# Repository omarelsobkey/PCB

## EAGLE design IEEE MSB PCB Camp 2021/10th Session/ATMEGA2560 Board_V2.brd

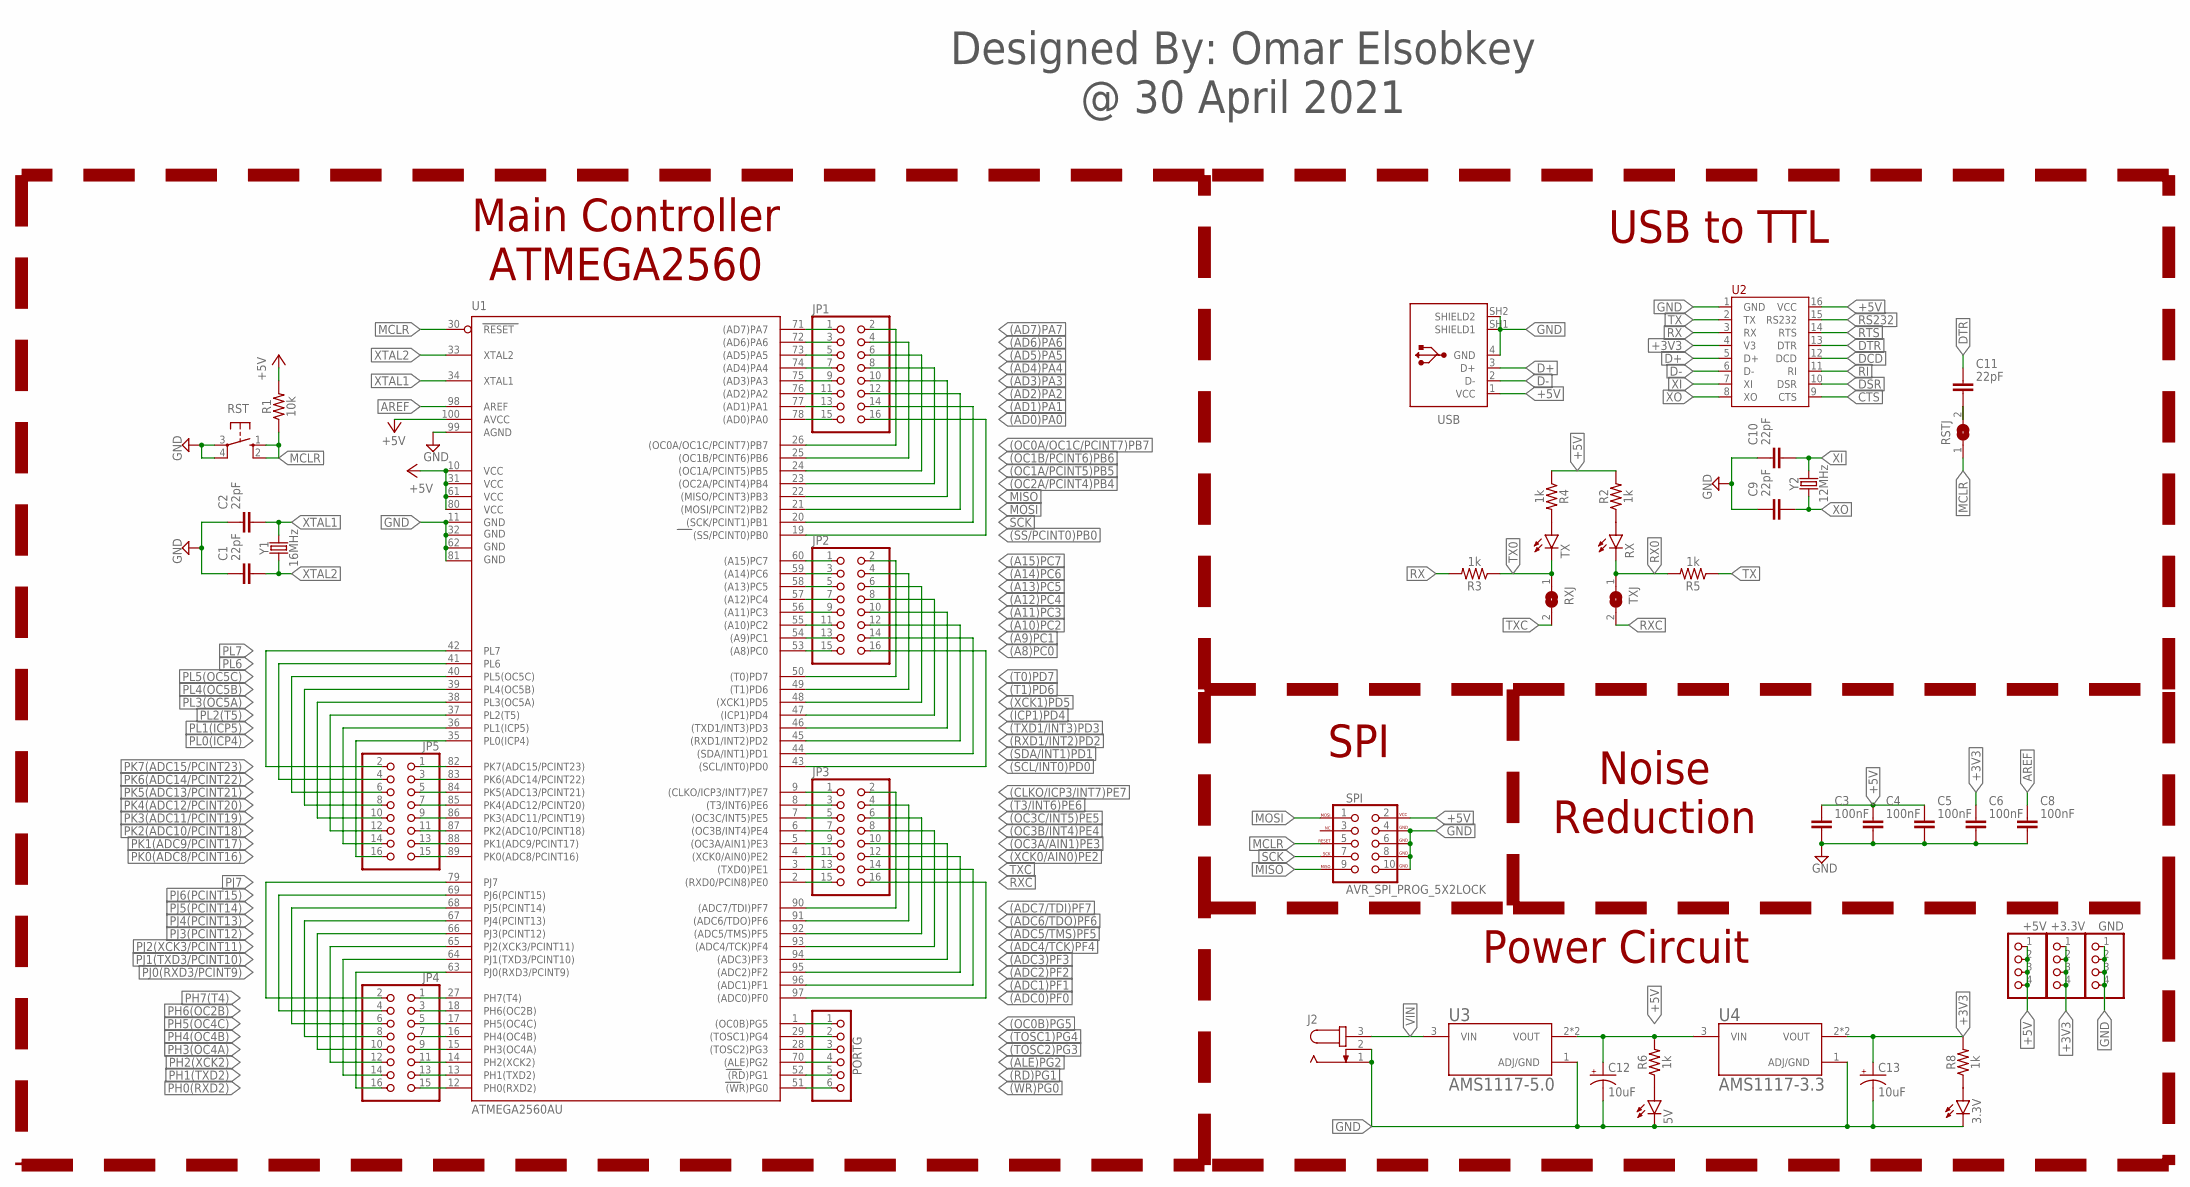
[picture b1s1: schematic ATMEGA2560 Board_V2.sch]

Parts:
3.3V, 5V: LEDCHIP-LED0805; CHIP-LED0805
+3.3V, +5V: PINHD-1X4; 1X04
C1, C2, C9, C10, C11: 22pF; CAPC2012X110
C3, C4, C5, C6, C8: 100nF; CAPC2012X110
C12, C13: 10uF; CPOL-RADIAL-2.5MM-5MM-KIT
GND: PINHD-1X4; 1X04
J2: JACK-PLUG0; SPC4077
JP1, JP2, JP3, JP4, JP5: PINHD-2X8; 2X08
PORTG: PINHD-1X6; 1X06
R1: 10k; 1206
R2, R3, R4, R5, R6, R8: 1k; 1206
RST: 10-XX; B3F-10XX
RSTJ: SJW
RX: LEDCHIP-LED0805; CHIP-LED0805
RXJ: SJW
SPI: AVR_SPI_PROG_5X2LOCK; 2X5-SHROUDED_LOCK
TX: LEDCHIP-LED0805; CHIP-LED0805
TXJ: SJW
U1: ATMEGA2560AU; TQFP100
U2: CH340G; SOP-16
U3: AMS1117-5.0
U4: AMS1117-3.3; AMS1117-5.0
USB: 61729-1011; 61729-1011BLF
Y1: 16MHz; HC49U
Y2: 12MHz; HC49U

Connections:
(A8)PC0: JP2.15, U1.53 ((A8)PC0)
(A9)PC1: JP2.13, U1.54 ((A9)PC1)
(A10)PC2: JP2.11, U1.55 ((A10)PC2)
(A11)PC3: JP2.9, U1.56 ((A11)PC3)
(A12)PC4: JP2.7, U1.57 ((A12)PC4)
(A13)PC5: JP2.5, U1.58 ((A13)PC5)
(A14)PC6: JP2.3, U1.59 ((A14)PC6)
(A15)PC7: JP2.1, U1.60 ((A15)PC7)
(AD0)PA0: JP1.15, U1.78 ((AD0)PA0)
(AD1)PA1: JP1.13, U1.77 ((AD1)PA1)
(AD2)PA2: JP1.11, U1.76 ((AD2)PA2)
(AD3)PA3: JP1.9, U1.75 ((AD3)PA3)
(AD4)PA4: JP1.7, U1.74 ((AD4)PA4)
(AD5)PA5: JP1.5, U1.73 ((AD5)PA5)
(AD6)PA6: JP1.3, U1.72 ((AD6)PA6)
(AD7)PA7: JP1.1, U1.71 ((AD7)PA7)
(ADC0)PF0: JP3.16, U1.97 ((ADC0)PF0)
(ADC1)PF1: JP3.14, U1.96 ((ADC1)PF1)
(ADC2)PF2: JP3.12, U1.95 ((ADC2)PF2)
(ADC3)PF3: JP3.10, U1.94 ((ADC3)PF3)
(ADC4/TCK)PF4: JP3.8, U1.93 ((ADC4/TCK)PF4)
(ADC5/TMS)PF5: JP3.6, U1.92 ((ADC5/TMS)PF5)
(ADC6/TDO)PF6: JP3.4, U1.91 ((ADC6/TDO)PF6)
(ADC7/TDI)PF7: JP3.2, U1.90 ((ADC7/TDI)PF7)
(ALE)PG2: PORTG.4, U1.70 ((ALE)PG2)
(CLKO/ICP3/INT7)PE7: JP3.1, U1.9 ((CLKO/ICP3/INT7)PE7)
(ICP1)PD4: JP2.8, U1.47 ((ICP1)PD4)
(OC0A/OC1C/PCINT7)PB7: JP1.2, U1.26 ((OC0A/OC1C/PCINT7)PB7)
(OC0B)PG5: PORTG.1, U1.1 ((OC0B)PG5)
(OC1A/PCINT5)PB5: JP1.6, U1.24 ((OC1A/PCINT5)PB5)
(OC1B/PCINT6)PB6: JP1.4, U1.25 ((OC1B/PCINT6)PB6)
(OC2A/PCINT4)PB4: JP1.8, U1.23 ((OC2A/PCINT4)PB4)
(OC3A/AIN1)PE3: JP3.9, U1.5 ((OC3A/AIN1)PE3)
(OC3B/INT4)PE4: JP3.7, U1.6 ((OC3B/INT4)PE4)
(OC3C/INT5)PE5: JP3.5, U1.7 ((OC3C/INT5)PE5)
(RD)PG1: PORTG.5, U1.52 ((RD)PG1)
(RXD1/INT2)PD2: JP2.12, U1.45 ((RXD1/INT2)PD2)
(SCL/INT0)PD0: JP2.16, U1.43 ((SCL/INT0)PD0)
(SDA/INT1)PD1: JP2.14, U1.44 ((SDA/INT1)PD1)
(SS/PCINT0)PB0: JP1.16, U1.19 ((SS/PCINT0)PB0)
(T0)PD7: JP2.2, U1.50 ((T0)PD7)
(T1)PD6: JP2.4, U1.49 ((T1)PD6)
(T3/INT6)PE6: JP3.3, U1.8 ((T3/INT6)PE6)
(TOSC1)PG4: PORTG.2, U1.29 ((TOSC1)PG4)
(TOSC2)PG3: PORTG.3, U1.28 ((TOSC2)PG3)
(TXD1/INT3)PD3: JP2.10, U1.46 ((TXD1/INT3)PD3)
(WR)PG0: PORTG.6, U1.51 ((WR)PG0)
(XCK0/AIN0)PE2: JP3.11, U1.4 ((XCK0/AIN0)PE2)
(XCK1)PD5: JP2.6, U1.48 ((XCK1)PD5)
+3V3: +3.3V.1, +3.3V.2, +3.3V.3, +3.3V.4, C6.1, C13.1 (+), R8.2, U2.4 (V3), U4.2 (VOUT), U4.4 (VOUT)
+5V: +5V.1, +5V.2, +5V.3, +5V.4, C3.1, C4.1, C5.1, C12.1 (+), R1.2, R2.2, R4.1, R6.2, SPI.2 (VCC), U1.10 (VCC), U1.31 (VCC1), U1.61 (VCC2), U1.80 (VCC3), U1.100 (AVCC), U2.16 (VCC), U3.2 (VOUT), U3.4 (VOUT), U4.3 (VIN), USB.1 (VCC)
AREF: C8.1, U1.98 (AREF)
CTS: U2.9 (CTS)
D+: U2.5 (D+), USB.3 (D+)
D-: U2.6 (D-), USB.2 (D-)
DCD: U2.12 (DCD)
DSR: U2.10 (DSR)
DTR: C11.1, U2.13 (DTR)
GND: 3.3V.C, 5V.C, C1.1, C2.1, C3.2, C4.2, C5.2, C6.2, C8.2, C9.1, C10.1, C12.2 (-), C13.2 (-), GND.1, GND.2, GND.3, GND.4, J2.1, J2.2, RST.3, RST.4 (P1), SPI.4 (GND), SPI.6 (GND), SPI.8 (GND), SPI.10 (GND), U1.11 (GND), U1.32 (GND1), U1.62 (GND2), U1.81 (GND3), U1.99 (AGND), U2.1 (GND), U3.1 (ADJ/GND), U4.1 (ADJ/GND), USB.4 (GND), USB.SH1 (SHIELD1), USB.SH2 (SHIELD2)
MCLR: R1.1, RST.1 (S), RST.2 (S1), RSTJ.1, SPI.5 (RESET), U1.30 (RESET)
MISO: JP1.10, SPI.9 (MISO), U1.22 ((MISO/PCINT3)PB3)
MOSI: JP1.12, SPI.1 (MOSI), U1.21 ((MOSI/PCINT2)PB2)
unnamed: R2.1, RX.A
unnamed: R4.2, TX.A
unnamed: 5V.A, R6.1
unnamed: 3.3V.A, R8.1
unnamed: C11.2, RSTJ.2
PH0(RXD2): JP4.15, U1.12 (PH0(RXD2))
PH1(TXD2): JP4.13, U1.13 (PH1(TXD2))
PH2(XCK2): JP4.11, U1.14 (PH2(XCK2))
PH3(OC4A): JP4.9, U1.15 (PH3(OC4A))
PH4(OC4B): JP4.7, U1.16 (PH4(OC4B))
PH5(OC4C): JP4.5, U1.17 (PH5(OC4C))
PH6(OC2B): JP4.3, U1.18 (PH6(OC2B))
PH7(T4): JP4.1, U1.27 (PH7(T4))
PJ0(RXD3/PCINT9): JP4.16, U1.63 (PJ0(RXD3/PCINT9))
PJ1(TXD3/PCINT10): JP4.14, U1.64 (PJ1(TXD3/PCINT10))
PJ2(XCK3/PCINT11): JP4.12, U1.65 (PJ2(XCK3/PCINT11))
PJ3(PCINT12): JP4.10, U1.66 (PJ3(PCINT12))
PJ4(PCINT13): JP4.8, U1.67 (PJ4(PCINT13))
PJ5(PCINT14): JP4.6, U1.68 (PJ5(PCINT14))
PJ6(PCINT15): JP4.4, U1.69 (PJ6(PCINT15))
PJ7: JP4.2, U1.79 (PJ7)
PK0(ADC8/PCINT16): JP5.15, U1.89 (PK0(ADC8/PCINT16))
PK1(ADC9/PCINT17): JP5.13, U1.88 (PK1(ADC9/PCINT17))
PK2(ADC10/PCINT18): JP5.11, U1.87 (PK2(ADC10/PCINT18))
PK3(ADC11/PCINT19): JP5.9, U1.86 (PK3(ADC11/PCINT19))
PK4(ADC12/PCINT20): JP5.7, U1.85 (PK4(ADC12/PCINT20))
PK5(ADC13/PCINT21): JP5.5, U1.84 (PK5(ADC13/PCINT21))
PK6(ADC14/PCINT22): JP5.3, U1.83 (PK6(ADC14/PCINT22))
PK7(ADC15/PCINT23): JP5.1, U1.82 (PK7(ADC15/PCINT23))
PL0(ICP4): JP5.16, U1.35 (PL0(ICP4))
PL1(ICP5): JP5.14, U1.36 (PL1(ICP5))
PL2(T5): JP5.12, U1.37 (PL2(T5))
PL3(OC5A): JP5.10, U1.38 (PL3(OC5A))
PL4(OC5B): JP5.8, U1.39 (PL4(OC5B))
PL5(OC5C): JP5.6, U1.40 (PL5(OC5C))
PL6: JP5.4, U1.41 (PL6)
PL7: JP5.2, U1.42 (PL7)
RI: U2.11 (RI)
RS232: U2.15 (RS232)
RTS: U2.14 (RTS)
RX: R3.2, U2.3 (RX)
RX0: R5.2, RX.C, TXJ.1
RXC: JP3.15, TXJ.2, U1.2 ((RXD0/PCIN8)PE0)
SCK: JP1.14, SPI.7 (SCK), U1.20 ((SCK/PCINT1)PB1)
TX: R5.1, U2.2 (TX)
TX0: R3.1, RXJ.1, TX.C
TXC: JP3.13, RXJ.2, U1.3 ((TXD0)PE1)
VIN: J2.3, U3.3 (VIN)
XI: C10.2, U2.7 (XI), Y2.2
XO: C9.2, U2.8 (XO), Y2.1
XTAL1: C2.2, U1.34 (XTAL1), Y1.2
XTAL2: C1.2, U1.33 (XTAL2), Y1.1

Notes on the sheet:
Main Controller ATMEGA2560
USB to TTL
SPI
Noise Reduction
Power Circuit
Designed By: Omar Elsobkey @ 30 April 2021

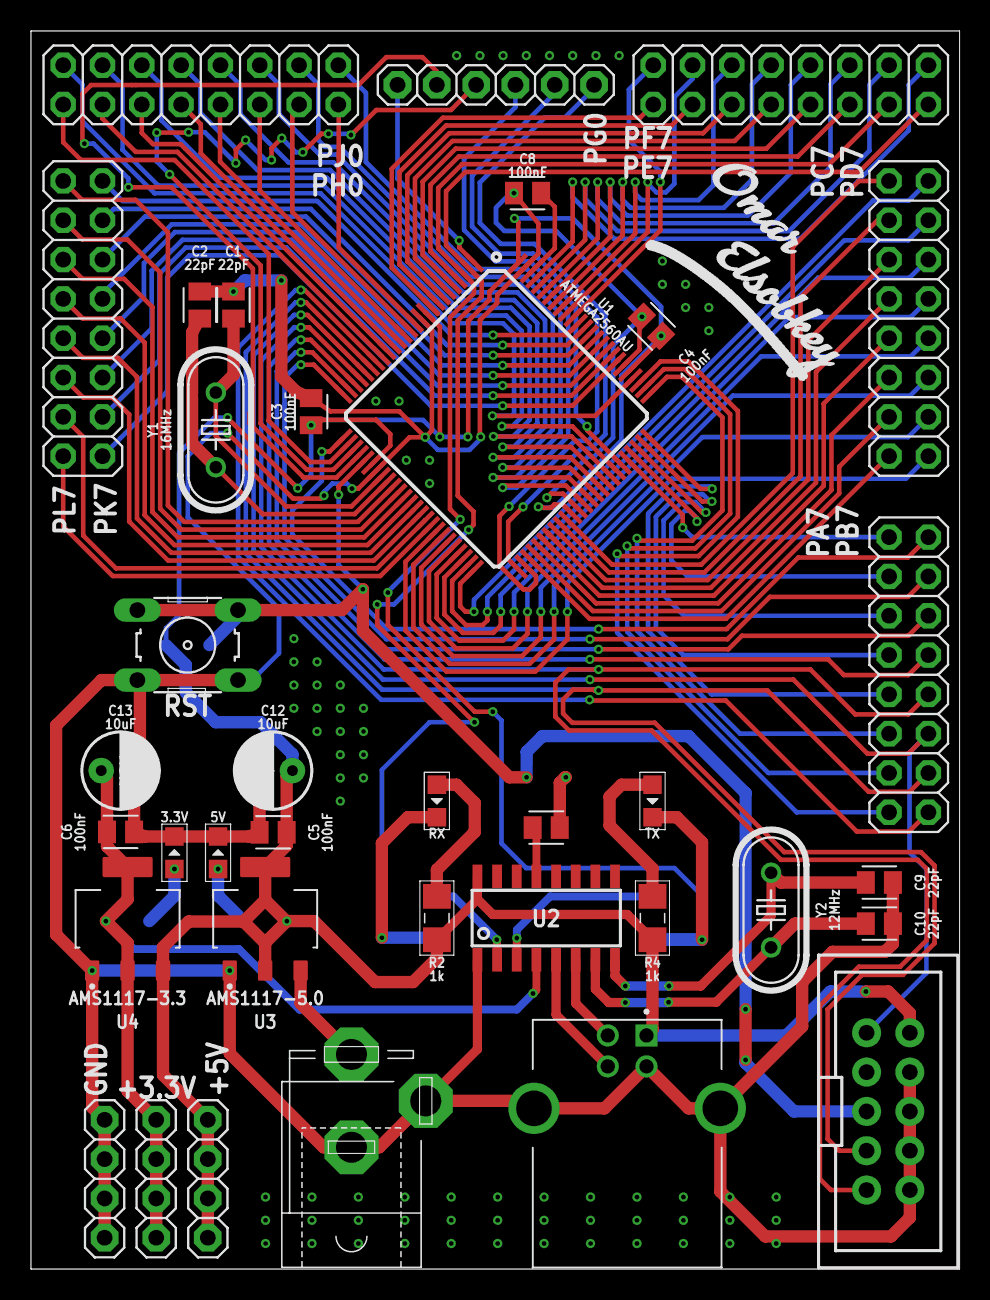
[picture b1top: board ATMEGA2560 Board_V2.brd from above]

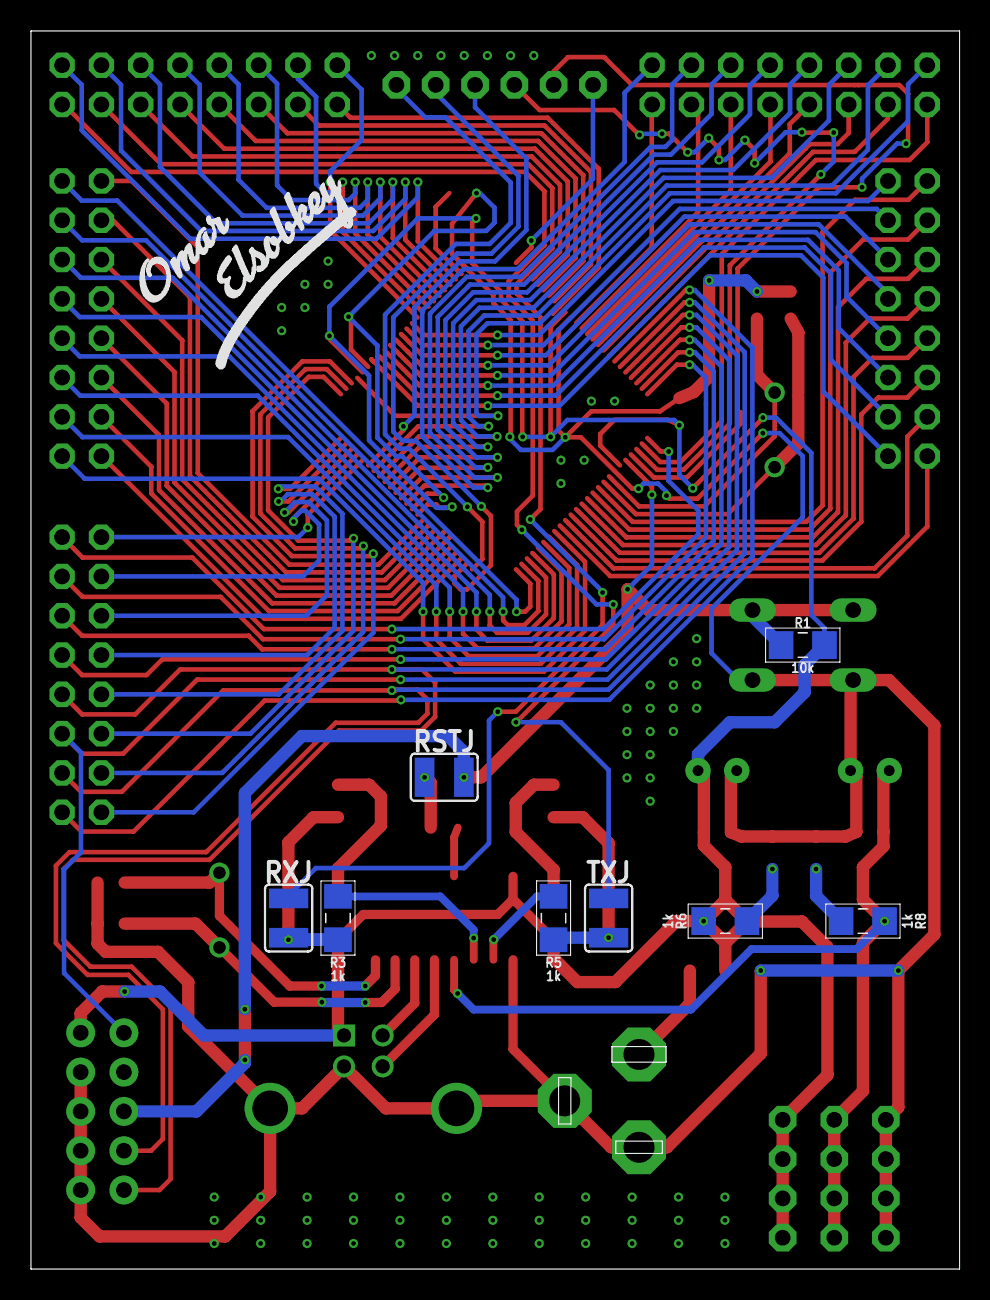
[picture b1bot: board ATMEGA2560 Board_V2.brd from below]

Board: 2 copper layers, 60.0 x 80.0 mm, 47 parts (9 on the bottom side), 108 nets.

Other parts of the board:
U$1, U$2: OMAR_ELSOBKEY_X1

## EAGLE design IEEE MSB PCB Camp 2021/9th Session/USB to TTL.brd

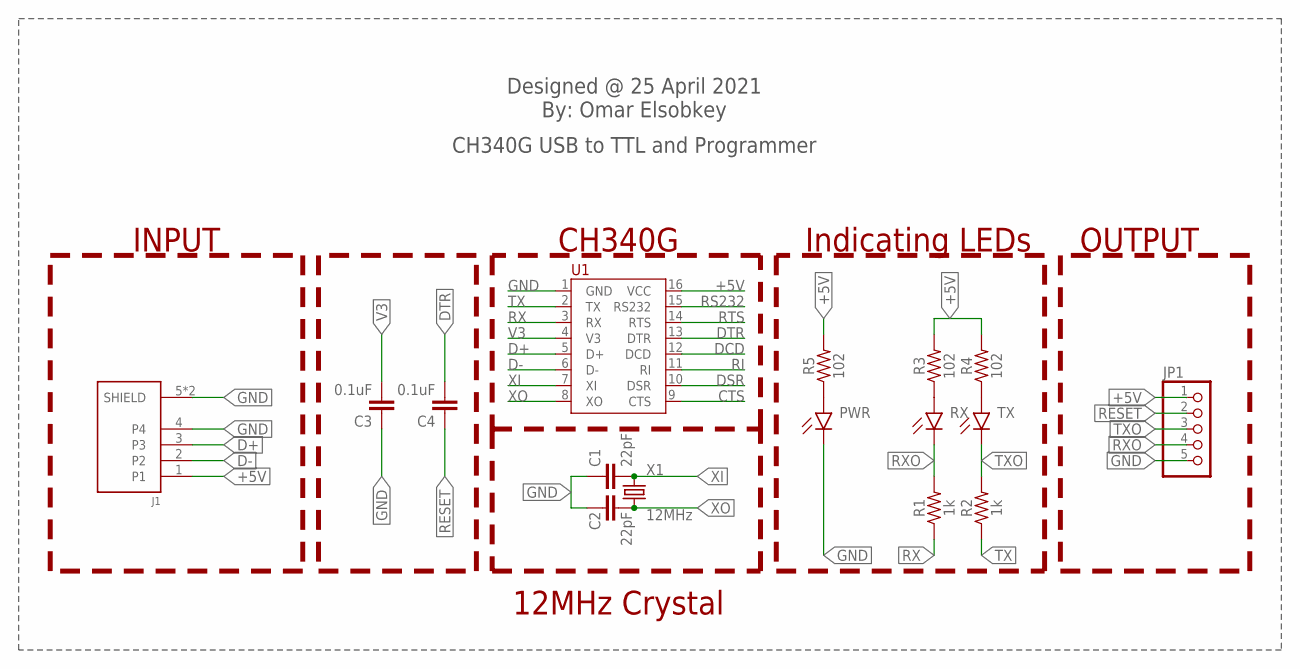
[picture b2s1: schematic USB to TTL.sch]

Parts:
C1, C2: 22pF; CAP-PTH-2.54
C3, C4: 0.1uF; CAP-PTH-SMALL-KIT
J1: 0480371000
JP1: PINHD-1X5/90; 1X05/90
PWR: CHIP-FLAT-B_0805; LEDC2012X110N_FLAT-B
R1, R2: 1k; 1206
R3, R4, R5: 102; 1206
RX: CHIP-FLAT-B_0805; LEDC2012X110N_FLAT-B
TX: CHIP-FLAT-B_0805; LEDC2012X110N_FLAT-B
U1: CH340G; SOP-16
X1: 12MHz; XTAL_HC49

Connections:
+5V: J1.1, JP1.1, R3.2, R4.2, R5.2, U1.16 (VCC)
CTS: U1.9 (CTS)
D+: J1.3, U1.5 (D+)
D-: J1.2, U1.6 (D-)
DCD: U1.12 (DCD)
DSR: U1.10 (DSR)
DTR: C4.2, U1.13 (DTR)
GND: C1.1, C2.1, C3.1, J1.4, J1.5 (SHIELD), J1.6 (SHIELD), JP1.5, PWR.C, U1.1 (GND)
unnamed: R3.1, RX.A
unnamed: R4.1, TX.A
unnamed: PWR.A, R5.1
RESET: C4.1, JP1.2
RI: U1.11 (RI)
RS232: U1.15 (RS232)
RTS: U1.14 (RTS)
RX: R1.1, U1.3 (RX)
RXO: JP1.4, R1.2, RX.C
TX: R2.1, U1.2 (TX)
TXO: JP1.3, R2.2, TX.C
V3: C3.2, U1.4 (V3)
XI: C1.2, U1.7 (XI), X1.2
XO: C2.2, U1.8 (XO), X1.1

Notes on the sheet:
Designed @ 25 April 2021 By: Omar Elsobkey
CH340G USB to TTL and Programmer
INPUT
CH340G
12MHz Crystal
Indicating LEDs
OUTPUT

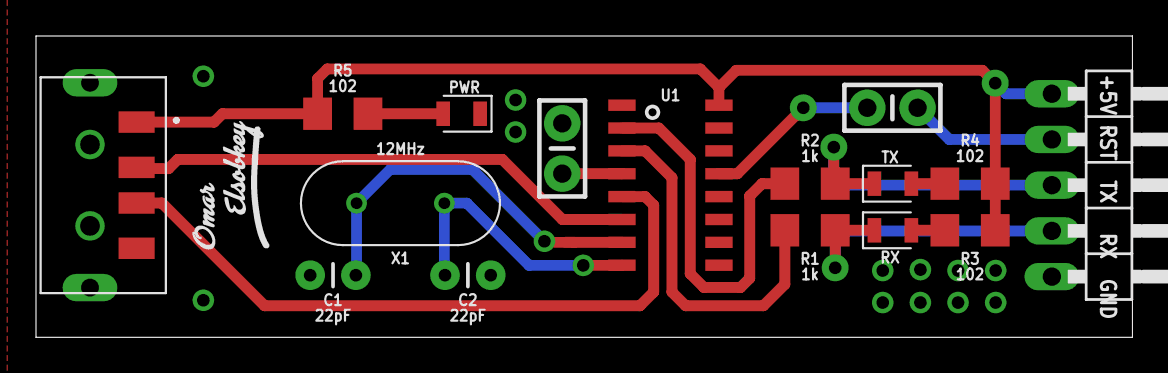
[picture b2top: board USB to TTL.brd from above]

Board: 2 copper layers, 60.9 x 16.7 mm, 18 parts (1 on the bottom side), 16 nets.

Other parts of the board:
U$1, U$2: OMAR_ELSOBKEY_X0.5_TN

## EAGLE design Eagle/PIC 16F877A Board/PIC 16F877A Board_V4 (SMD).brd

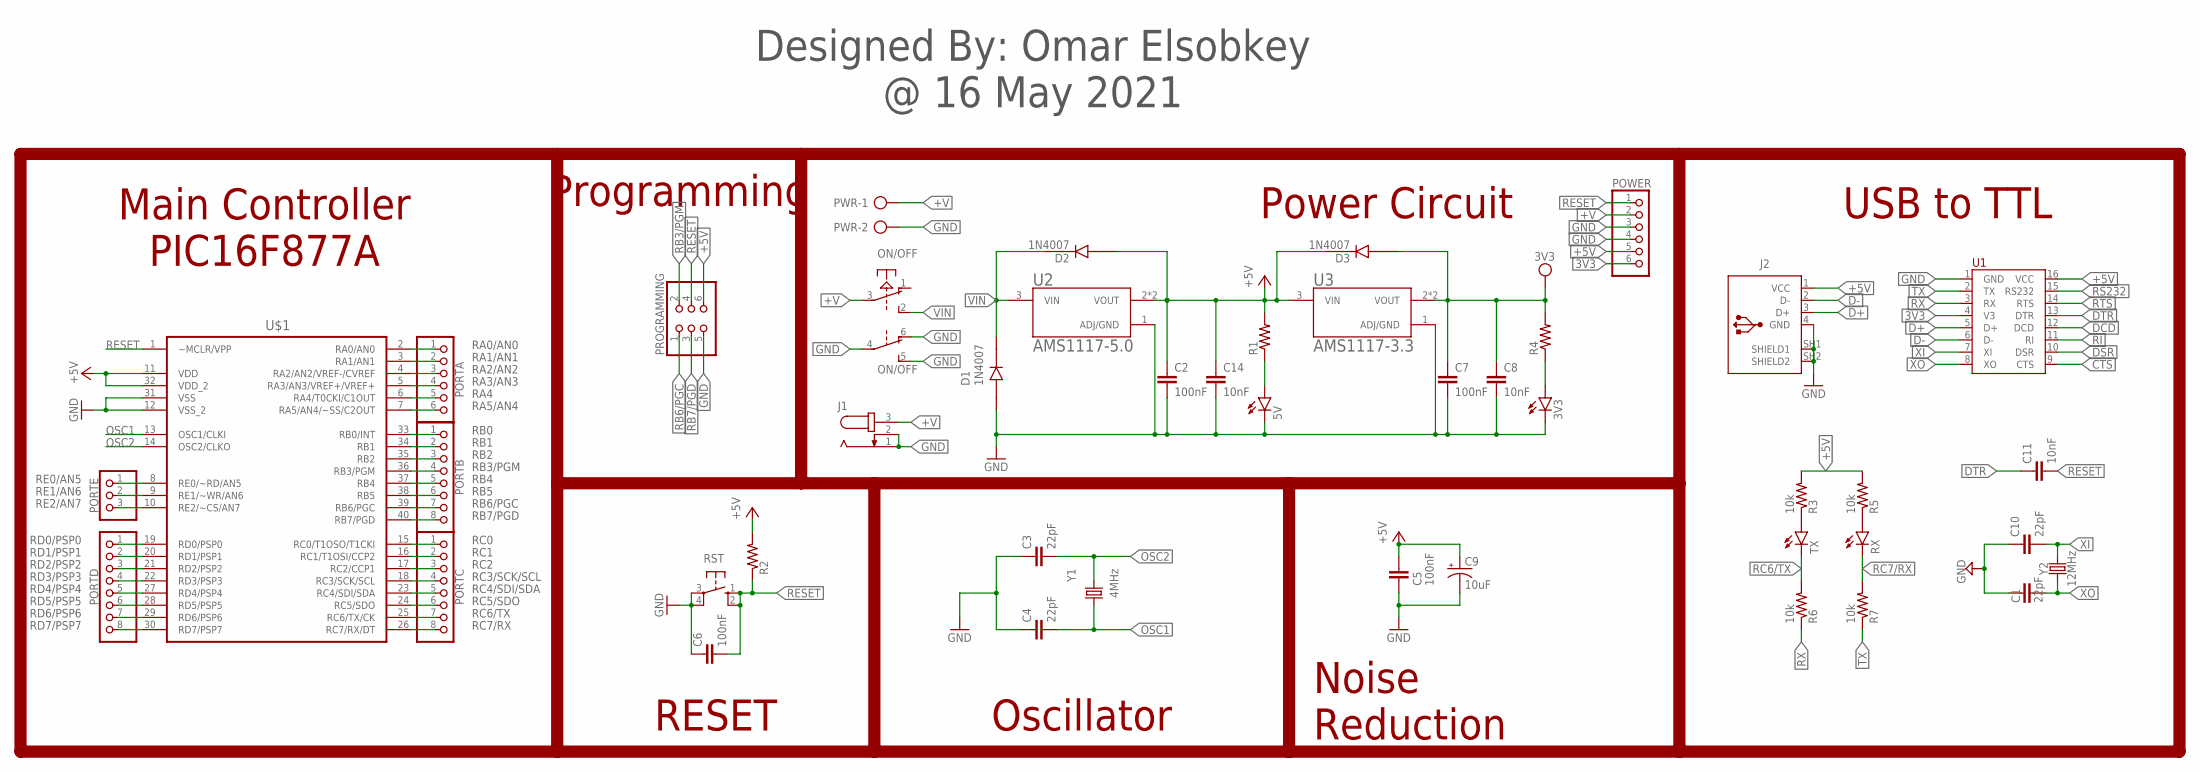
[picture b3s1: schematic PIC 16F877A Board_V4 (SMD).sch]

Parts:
3V3, 5V: LEDSML0805; SML0805
C1, C3, C4, C10: 22pF; CAPC2012X110
C2, C5, C6, C7: 100nF; CAPC2012X110
C8, C11, C14: 10nF; CAPC2012X110
C9: 10uF; CPOL-RADIAL-2.5MM-5MM-KIT
D1, D2, D3: 1N4007; SMA/DO-214AC
J1: JACK-PLUG0; SPC4077
J2: 61729-1011; 61729-1011BLF
ON/OFF: PVA2R
PORTA: PINHD-1X6; 1X06
PORTB: PINHD-1X8; 1X08
PORTC: PINHD-1X8; 1X08
PORTD: PINHD-1X8; 1X08
PORTE: PINHD-1X3; 1X03
POWER: PINHD-1X6; 1X06
PROGRAMMING: PINHD-2X3; 2X03
PWR: AK500/2-H
R1, R2, R4: 1206
R3, R5, R6, R7: 10k; 1206
RST: 10-XX; B3F-10XX
RX: LEDSML0805; SML0805
TX: LEDSML0805; SML0805
U1: CH340G; SOP-16
U2: AMS1117-5.0
U3: AMS1117-3.3; AMS1117-5.0
U$1: PIC16F877A-I/P; PDIP-40
Y1: 4MHz; HC49U
Y2: 12MHz; HC49U

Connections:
3V3: C7.1, C8.1, D3.2 (A), POWER.6, R4.2, U1.4 (V3), U3.2 (VOUT), U3.4 (VOUT)
+5V: C2.1, C5.2, C9.1 (+), C14.1, D2.2 (A), D3.1 (C), J2.1 (VCC), POWER.5, PROGRAMMING.6, R1.2, R2.2, R3.2, R5.2, U1.16 (VCC), U2.2 (VOUT), U2.4 (VOUT), U3.3 (VIN), U$1.11 (VDD), U$1.32 (VDD_2)
+V: J1.3, ON/OFF.3, POWER.2, PWR.1
CTS: U1.9 (CTS)
D+: J2.3 (D+), U1.5 (D+)
D-: J2.2 (D-), U1.6 (D-)
DCD: U1.12 (DCD)
DSR: U1.10 (DSR)
DTR: C11.1, U1.13 (DTR)
GND: 3V3.C, 5V.C, C1.1, C2.2, C3.1, C4.1, C5.1, C6.1, C7.2, C8.2, C9.2 (-), C10.1, C14.2, D1.2 (A), J1.1, J1.2, J2.4 (GND), J2.SH1 (SHIELD1), J2.SH2 (SHIELD2), ON/OFF.4, ON/OFF.5 (S), ON/OFF.6 (O), POWER.3, POWER.4, PROGRAMMING.5, PWR.2, RST.3, RST.4 (P1), U1.1 (GND), U2.1 (ADJ/GND), U3.1 (ADJ/GND), U$1.12 (VSS_2), U$1.31 (VSS)
unnamed: 3V3.A, R4.1
unnamed: R3.1, TX.A
unnamed: R5.1, RX.A
unnamed: 5V.A, R1.1
OSC1: C4.2, U$1.13 (OSC1/CLKI), Y1.2
OSC2: C3.2, U$1.14 (OSC2/CLKO), Y1.1
RA0/AN0: PORTA.1, U$1.2 (RA0/AN0)
RA1/AN1: PORTA.2, U$1.3 (RA1/AN1)
RA2/AN2: PORTA.3, U$1.4 (RA2/AN2/VREF-/CVREF)
RA3/AN3: PORTA.4, U$1.5 (RA3/AN3/VREF+/VREF+)
RA4: PORTA.5, U$1.6 (RA4/T0CKI/C1OUT)
RA5/AN4: PORTA.6, U$1.7 (RA5/AN4/~SS/C2OUT)
RB0: PORTB.1, U$1.33 (RB0/INT)
RB1: PORTB.2, U$1.34 (RB1)
RB2: PORTB.3, U$1.35 (RB2)
RB3/PGM: PORTB.4, PROGRAMMING.2, U$1.36 (RB3/PGM)
RB4: PORTB.5, U$1.37 (RB4)
RB5: PORTB.6, U$1.38 (RB5)
RB6/PGC: PORTB.7, PROGRAMMING.1, U$1.39 (RB6/PGC)
RB7/PGD: PORTB.8, PROGRAMMING.3, U$1.40 (RB7/PGD)
RC0: PORTC.1, U$1.15 (RC0/T1OSO/T1CKI)
RC1: PORTC.2, U$1.16 (RC1/T1OSI/CCP2)
RC2: PORTC.3, U$1.17 (RC2/CCP1)
RC3/SCK/SCL: PORTC.4, U$1.18 (RC3/SCK/SCL)
RC4/SDI/SDA: PORTC.5, U$1.23 (RC4/SDI/SDA)
RC5/SDO: PORTC.6, U$1.24 (RC5/SDO)
RC6/TX: PORTC.7, R6.2, TX.C, U$1.25 (RC6/TX/CK)
RC7/RX: PORTC.8, R7.2, RX.C, U$1.26 (RC7/RX/DT)
RD0/PSP0: PORTD.1, U$1.19 (RD0/PSP0)
RD1/PSP1: PORTD.2, U$1.20 (RD1/PSP1)
RD2/PSP2: PORTD.3, U$1.21 (RD2/PSP2)
RD3/PSP3: PORTD.4, U$1.22 (RD3/PSP3)
RD4/PSP4: PORTD.5, U$1.27 (RD4/PSP4)
RD5/PSP5: PORTD.6, U$1.28 (RD5/PSP5)
RD6/PSP6: PORTD.7, U$1.29 (RD6/PSP6)
RD7/PSP7: PORTD.8, U$1.30 (RD7/PSP7)
RE0/AN5: PORTE.1, U$1.8 (RE0/~RD/AN5)
RE1/AN6: PORTE.2, U$1.9 (RE1/~WR/AN6)
RE2/AN7: PORTE.3, U$1.10 (RE2/~CS/AN7)
RESET: C6.2, C11.2, POWER.1, PROGRAMMING.4, R2.1, RST.1 (S), RST.2 (S1), U$1.1 (~MCLR/VPP)
RI: U1.11 (RI)
RS232: U1.15 (RS232)
RTS: U1.14 (RTS)
RX: R6.1, U1.3 (RX)
TX: R7.1, U1.2 (TX)
VIN: D1.1 (C), D2.1 (C), ON/OFF.2 (S), U2.3 (VIN)
XI: C10.2, U1.7 (XI), Y2.2
XO: C1.2, U1.8 (XO), Y2.1

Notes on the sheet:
Main Controller PIC16F877A
Power Circuit
RESET
Oscillator
Noise Reduction
Programming
Designed By: Omar Elsobkey @ 16 May 2021
USB to TTL

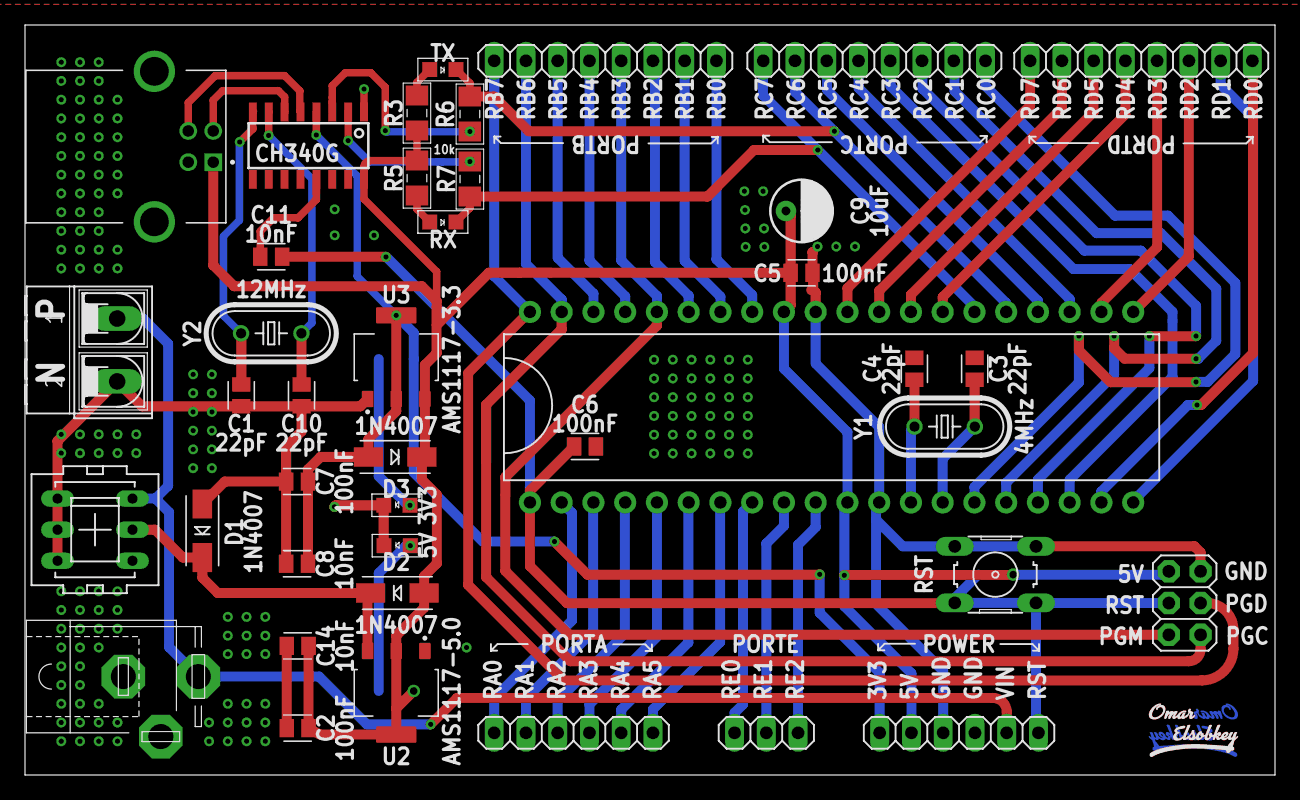
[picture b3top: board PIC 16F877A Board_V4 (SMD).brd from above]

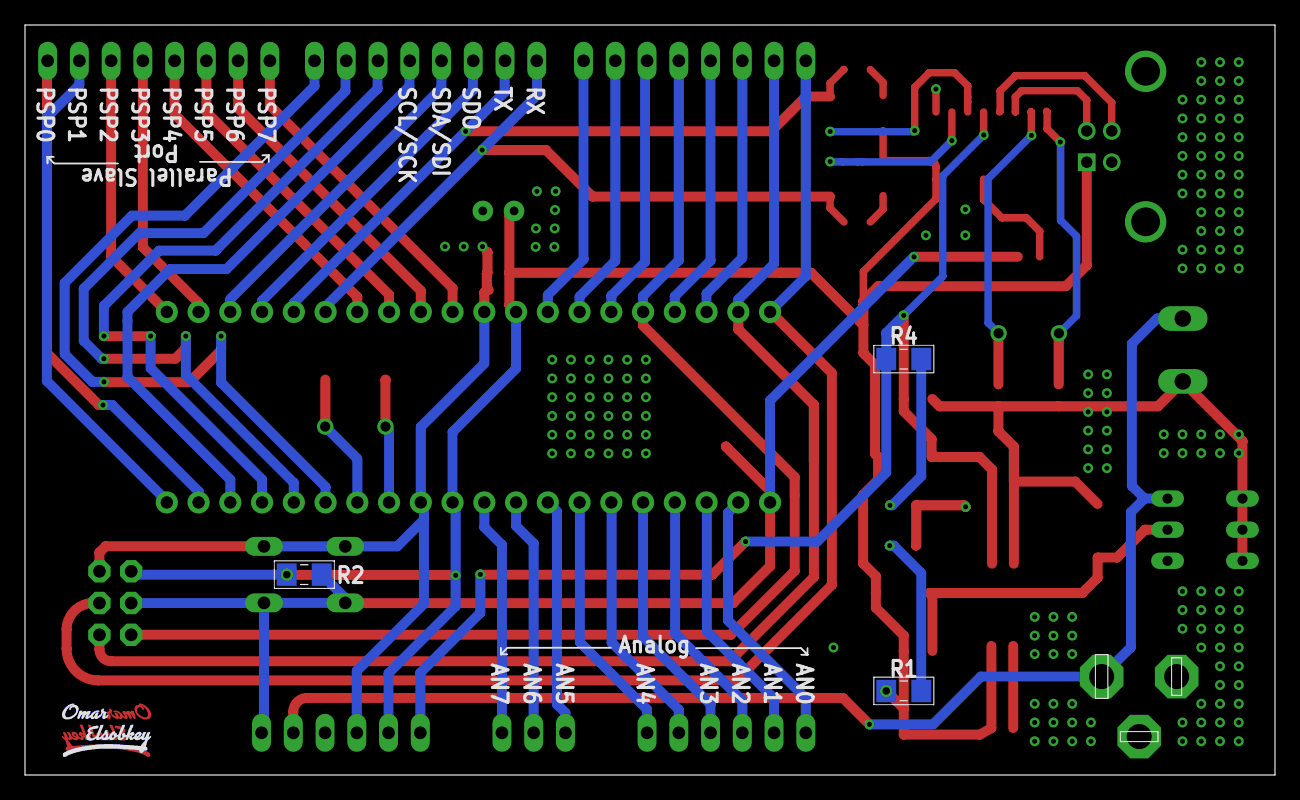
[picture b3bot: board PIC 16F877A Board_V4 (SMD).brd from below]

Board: 2 copper layers, 100.0 x 60.0 mm, 48 parts (5 on the bottom side), 52 nets.

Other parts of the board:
U$2, U$4: OMAR_ELSOBKEY_X0.5_T
U$3, U$5: OMAR_ELSOBKEY_X0.5_TN

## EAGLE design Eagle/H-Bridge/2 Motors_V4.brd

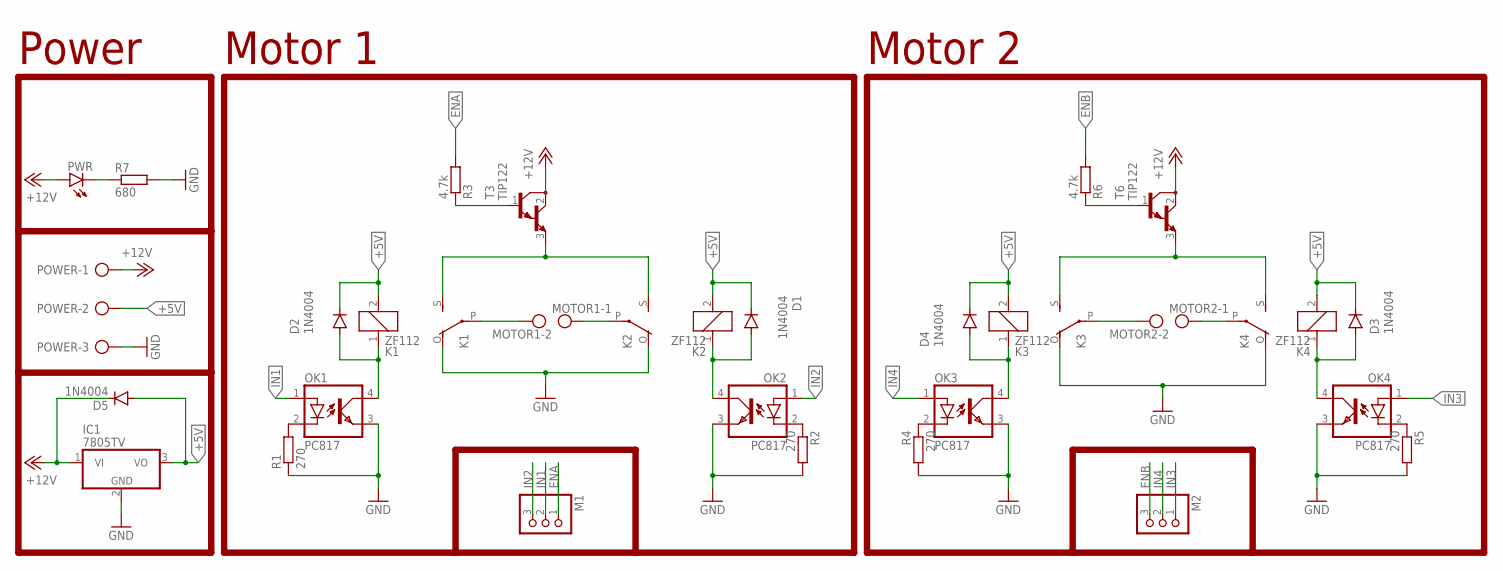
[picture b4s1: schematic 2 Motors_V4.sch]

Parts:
D1, D2, D3, D4, D5: 1N4004; DO41-10
IC1: 7805TV; TO220V
K1, K2, K3, K4: ZF112
M1, M2: PINHD-1X3; 1X03
MOTOR1, MOTOR2: AK300/2
OK1, OK2, OK3, OK4: PC817; DIL04
POWER: AK300/3
PWR: LED5MM
R1, R2, R4, R5: 270; 0204/7
R3, R6: 4.7k; 0204/7
R7: 680; 0204/7
T3, T6: TIP122; TO220

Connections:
+5V: D1.C, D2.C, D3.C, D4.C, D5.A, IC1.3 (VO), K1.2, K2.2, K3.2, K4.2, POWER.2
+12V: D5.C, IC1.1 (VI), POWER.1, PWR.A, T3.2 (C), T6.2 (C)
ENA: M1.1, R3.2
ENB: M2.3, R6.2
GND: IC1.2 (GND), K1.O, K2.O, K3.O, K4.O, OK1.3 (EMIT), OK2.3 (EMIT), OK3.3 (EMIT), OK4.3 (EMIT), POWER.3, R1.1, R2.2, R4.2, R5.2, R7.2
IN1: M1.2, OK1.1 (A)
IN2: M1.3, OK2.1 (A)
IN3: M2.1, OK4.1 (A)
IN4: M2.2, OK3.1 (A)
unnamed: K1.P, MOTOR1.2
unnamed: K1.S, K2.S, T3.3 (E)
unnamed: D2.A, K1.1, OK1.4 (COL)
unnamed: PWR.K (C), R7.1
unnamed: K2.P, MOTOR1.1
unnamed: D1.A, K2.1, OK2.4 (COL)
unnamed: D3.A, K4.1, OK4.4 (COL)
unnamed: K3.S, K4.S, T6.3 (E)
unnamed: D4.A, K3.1, OK3.4 (COL)
unnamed: OK1.2 (C), R1.2
unnamed: OK2.2 (C), R2.1
unnamed: OK4.2 (C), R5.1
unnamed: OK3.2 (C), R4.1
unnamed: K4.P, MOTOR2.1
unnamed: K3.P, MOTOR2.2
T3: R3.1, T3.1 (B)
T6: R6.1, T6.1 (B)

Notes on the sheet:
Power
Motor 1
Motor 2

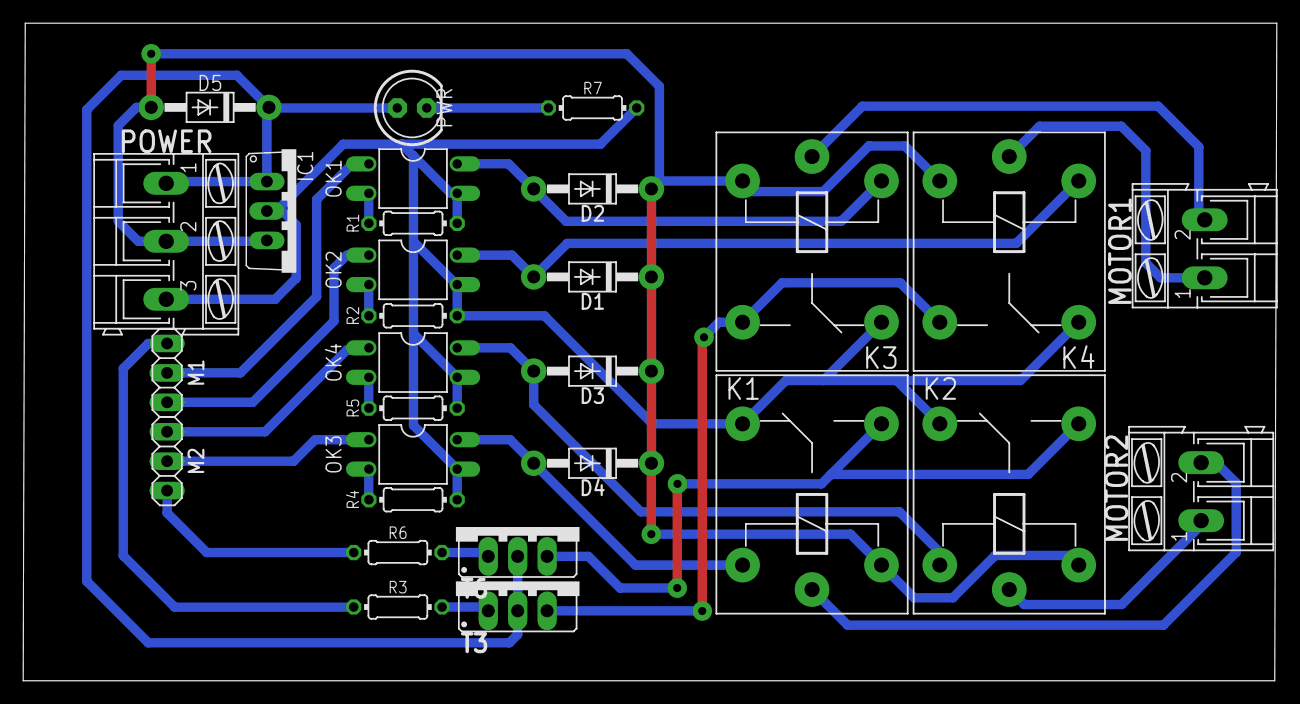
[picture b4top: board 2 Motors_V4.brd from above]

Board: 2 copper layers, 108.2 x 56.7 mm, 29 parts (0 on the bottom side), 26 nets.

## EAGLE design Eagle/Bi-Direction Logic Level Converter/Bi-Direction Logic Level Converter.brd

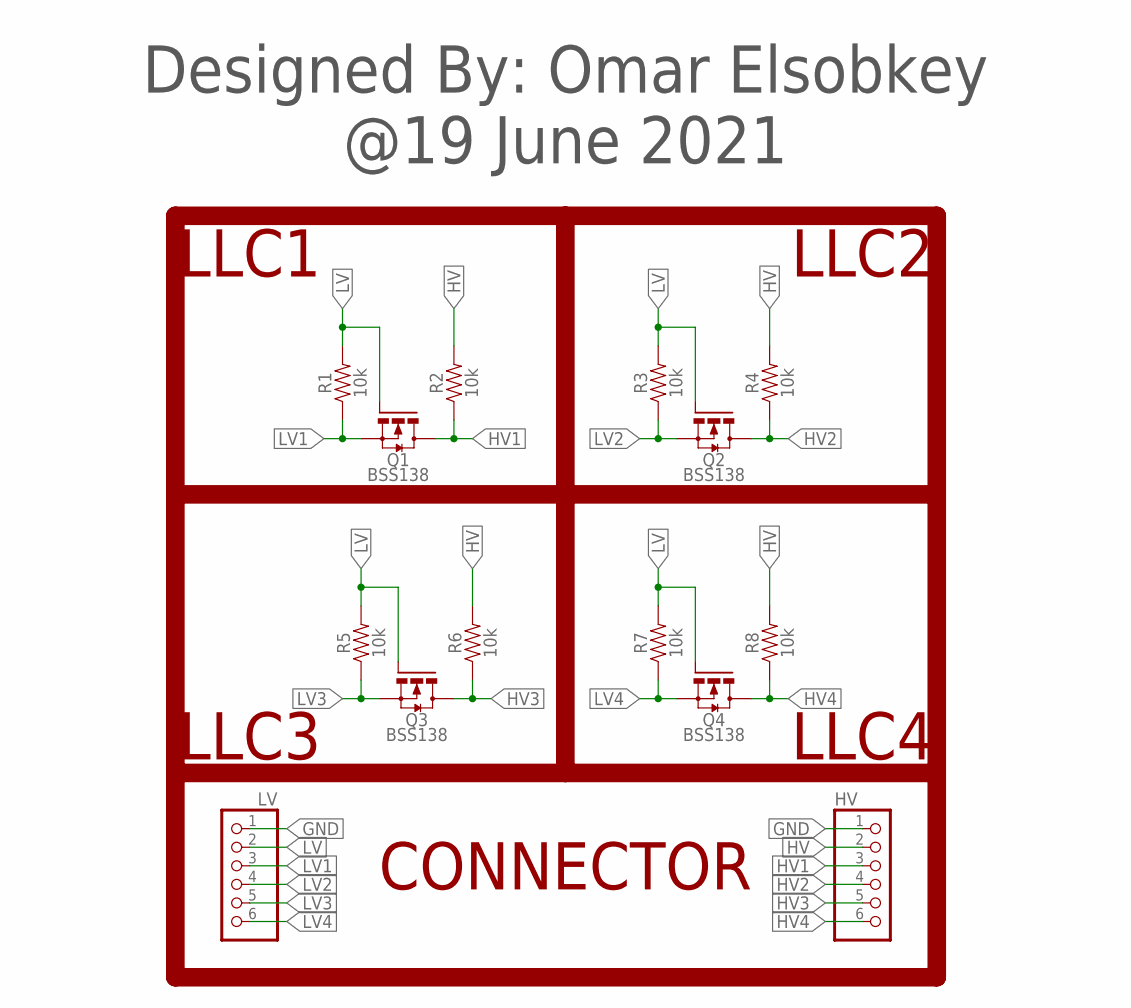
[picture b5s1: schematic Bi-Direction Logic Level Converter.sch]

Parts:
HV: PINHD-1X6; 1X06
LV: PINHD-1X6; 1X06
Q1, Q2, Q3, Q4: BSS138; SOT23-3
R1, R2, R3, R4, R5, R6, R7, R8: 10k; 1206

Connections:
GND: HV.1, LV.1
HV: HV.2, R2.2, R4.2, R6.2, R8.2
HV1: HV.3, Q1.3 (D), R2.1
HV2: HV.4, Q2.3 (D), R4.1
HV3: HV.5, Q3.3 (D), R6.1
HV4: HV.6, Q4.3 (D), R8.1
LV: LV.2, Q1.1 (G), Q2.1 (G), Q3.1 (G), Q4.1 (G), R1.2, R3.2, R5.2, R7.2
LV1: LV.3, Q1.2 (S), R1.1
LV2: LV.4, Q2.2 (S), R3.1
LV3: LV.5, Q3.2 (S), R5.1
LV4: LV.6, Q4.2 (S), R7.1

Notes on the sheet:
Designed By: Omar Elsobkey @19 June 2021
LLC1
LLC2
LLC3
LLC4
CONNECTOR

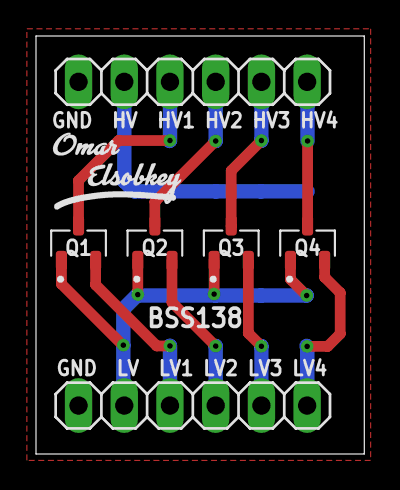
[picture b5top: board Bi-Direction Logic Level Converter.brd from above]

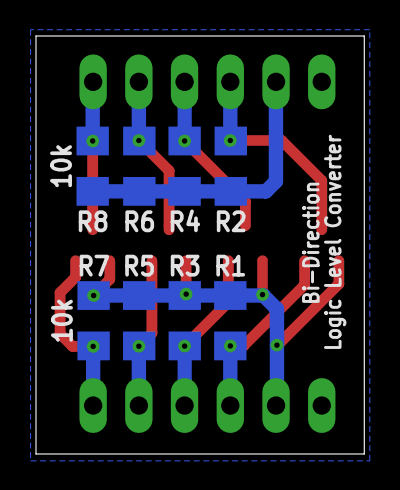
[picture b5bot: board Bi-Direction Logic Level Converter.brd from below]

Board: 2 copper layers, 18.2 x 23.2 mm, 15 parts (8 on the bottom side), 11 nets.

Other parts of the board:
U$1: OMAR_ELSOBKEY_X0.5_TN

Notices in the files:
parts and their libraries:
SparkFun-Resistors: Licensing: Creative Commons ShareAlike 4.0 International - https://creativecommons.org/licenses/by-sa/4.0
Wurth_Capacitors_WCAP-ATG8: Copyright: Würth Elektronik
